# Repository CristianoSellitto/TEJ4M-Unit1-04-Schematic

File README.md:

# TEJ4M-Unit1-04-Schematic

Contains the electronic schematic & PCB for Unit1-04

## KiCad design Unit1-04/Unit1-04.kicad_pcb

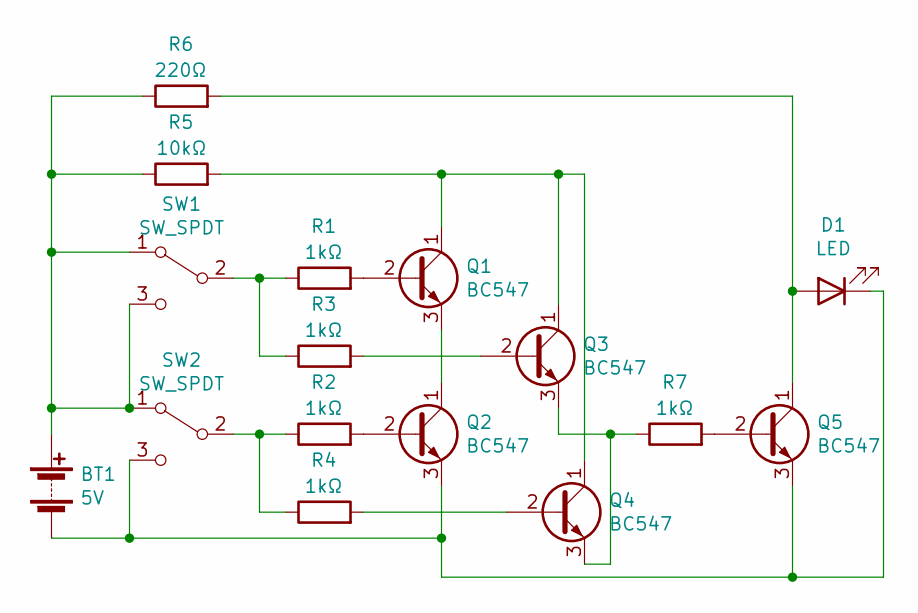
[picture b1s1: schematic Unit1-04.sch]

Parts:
BT1: 5V; BatteryHolder_Bulgin_BX0036_1xC
D1: LED; LED-L1T2_LUMILEDS
Q1, Q2, Q3, Q4, Q5: BC547; TO-92_Inline
R1, R2, R3, R4, R7: 1kΩ; R_0201_0603Metric_Pad0.64x0.40mm_HandSolder
R5: 10kΩ; R_0201_0603Metric_Pad0.64x0.40mm_HandSolder
R6: 220Ω; R_0201_0603Metric_Pad0.64x0.40mm_HandSolder
SW1, SW2: SW_SPDT; SW_SPDT_CK-JS102011SAQN

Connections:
unnamed: BT1.1 (+), R5.1, R6.1, SW1.1 (A), SW1.3 (C), SW2.1 (A)
unnamed: BT1.2 (-), D1.1 (K), Q2.3 (E), Q5.3 (E), SW2.3 (C)
unnamed: D1.2 (A), Q5.1 (C), R6.2
unnamed: Q1.1 (C), Q3.1 (C), Q4.1 (C), R5.2
unnamed: Q1.2 (B), R1.2
unnamed: Q1.3 (E), Q2.1 (C)
unnamed: Q2.2 (B), R2.2
unnamed: Q3.2 (B), R3.2
unnamed: Q3.3 (E), Q4.3 (E), R7.1
unnamed: Q4.2 (B), R4.2
unnamed: Q5.2 (B), R7.2
unnamed: R1.1, R3.1, SW1.2 (B)
unnamed: R2.1, R4.1, SW2.2 (B)

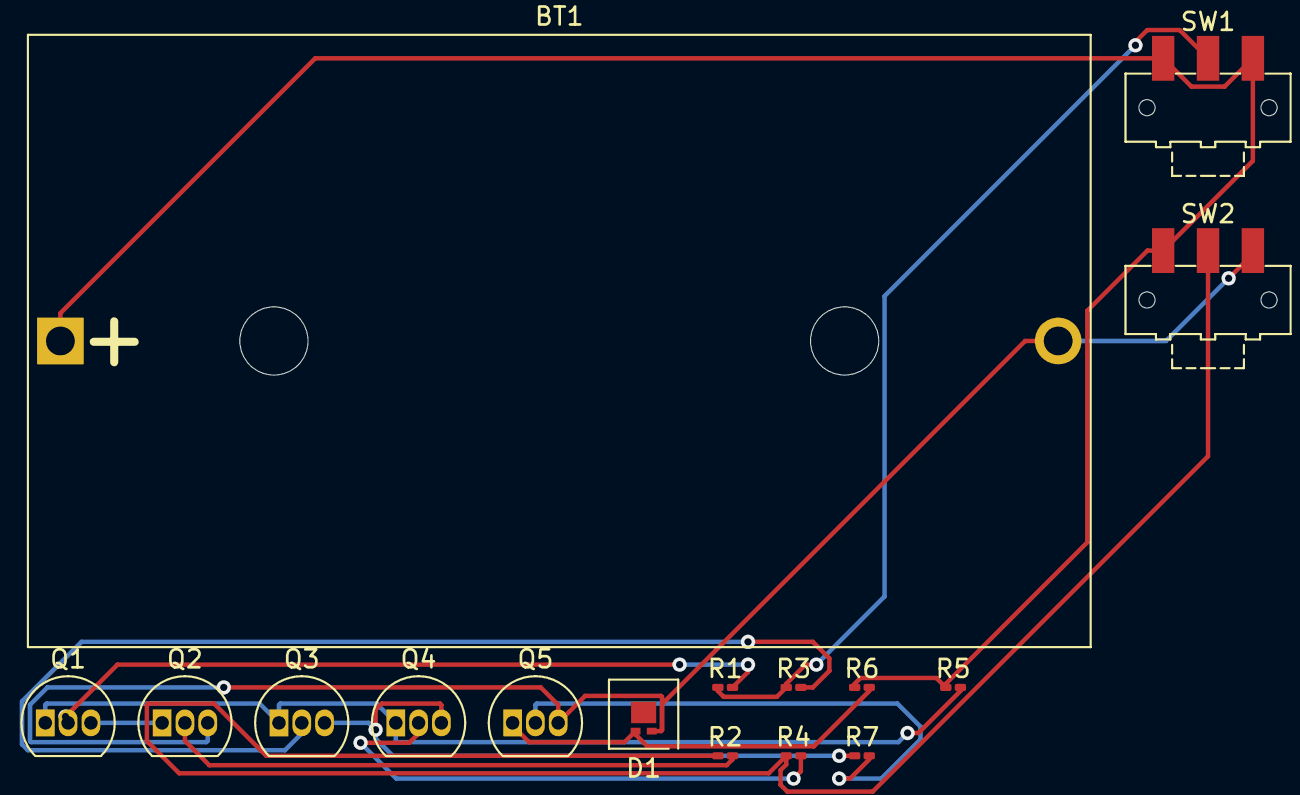
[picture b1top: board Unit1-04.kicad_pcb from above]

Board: 2 copper layers, 16 parts (0 on the bottom side), 13 nets.

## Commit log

2023-11-07 SSH Import
2023-11-08 Added PCB files
2023-11-08 Added comment on PCB
